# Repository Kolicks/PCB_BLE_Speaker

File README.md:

# 🔊 PCB_BLE_Speaker  
**BLE Audio + USB-C Rechargeable Speaker Board**

---

## 📘 Overview
**PCB_BLE_Speaker** is a compact **BLE audio speaker board** designed in **KiCad 9**, focused on learning about **USB-C**, **battery-powered systems**, **rechargeable devices**, and **audio amplifier integration**.  
The project explores practical design decisions such as **battery connectors**, **charging circuits**, **power protection**, and **audio MCU layout constraints**.

It includes two **MAX98357A** audio MCUs to experiment with both **mono** and **stereo firmware**, and was created as an exercise in **DFM/DFA**, power routing, and EMC-aware PCB design.

<p align="center">
  
  <br>
  <em>3D render of the PCB_BLE_Speaker board</em>
</p>

---

## ⚠️ FLAWS
- Serial Comms does not work, need extra circuitry for EN/BOOT between ESP32 and CP2102N.
- Be aware of the Audio connectors polarity. In this design you may need to solder on the opposite direction.

---

## ⚙️ General Information
- Designed in **KiCad 9** as a learning platform for:
  - USB-C 2.0 (5 V / 1 A)
  - Battery-powered systems
  - Rechargeable device architecture  
- Includes **two battery connectors**:  
  - One for a battery already owned  
  - One for a **standard battery connector** planned for purchase  
- Created to better understand **power protection**, **charging ICs**, and **audio layout constraints**.
- Built on a **4-layer PCB**, as recommended for the **MAX98357A** for better reliability, noise control, and ground integrity.
- All components intentionally placed on the **top layer** as a DFA/DFM exercise.

<p align="center">
  
  <br>
  <em>Schematic (KiCad 9)</em>
</p>

---

## 🔊 Characteristics
- **USB-C 2.0** input supplying **5 V up to 1 A**.  
- **MCP73831-2-OT** Li-Ion charger with a **5 kΩ PROG resistor**, giving a safe **200 mA charge current** — chosen to reduce thermal risks since no temperature monitoring system is implemented.  
- **MOSFET protection circuitry** between USB-C and charger to manage correct power flow and avoid dangerous battery–USB backfeed conditions.  
- **Two MAX98357A audio MCUs** included:
  - Allows experimenting with **mono** and **stereo** BLE audio firmware.
- Intended for **battery operation**:
  - A DC/DC regulator would have improved efficiency, but was intentionally discarded for version 1 for simplicity.
- Observed layout improvement for next revision:
  - Placing **audio amplifier + charger + power supply** side by side to reduce **current loop area**, improving **EMC/EMI** behavior and reducing high-current noise.

<p align="center">
  
  <br>
  <em>PCB layout design</em>
</p>

---

## ⚠️ Known Issues / Notes
- Power architecture can be improved by using a **buck DC/DC converter** for better efficiency during battery operation.  
- Current loops of the audio + charger power path could be optimized by placing related components closer.  
- Future improvements should include:
  - Better **EMI loop minimization**  
  - Dedicated copper pours for high-current paths  
  - Additional filtering  
- Placement of both audio MCUs on the top layer made routing more challenging, but was kept intentionally as a DFM/DFA practice exercise.
- Rechargable Battery circuitry WORKS as expected!
---

## 🧩 Files and Structure

<p align="center">
  
</p>

PCB_BLE_Speaker/
├── schematic/
├── pcb_layout/
├── gerbers/
├── images/
├── LICENSE
└── README.md

---

## 📜 License
This hardware design is released under the **CERN Open Hardware License v2 – Permissive (CERN-OHL-P-2.0)**.  
You may use, modify, and redistribute the design, as long as:
- You include the license in redistributions.
- You give proper credit to the original author.

---

## 👤 Author
**Project:** PCB_BLE_Speaker  
**Author:** Kolicks  
**Toolchain:** KiCad 9  
**Version:** 1.0  

---

## 🧱 Future Improvements
- **Power Efficiency**
  - Add a **buck DC/DC converter** to improve battery runtime and reduce heat.  
- **EMI-Aware Layout**
  - Place **charger + power supply + audio MCUs** adjacently to shrink high-current loops.  
- **User Indicators**
  - Add **charging, power, and battery status LEDs**.  
- **Battery Protection**
  - Add optional **NTC thermistor** for thermal monitoring.  
- **Usability**
  - Improve connector positioning and silkscreen clarity.
  - Add circuitry for Serial to make it reliable.
  - Change MCU to another one more suitable for Hand Soldering.

---

⭐ *If this project interests you, feel free to star the repository or contribute with suggestions!*

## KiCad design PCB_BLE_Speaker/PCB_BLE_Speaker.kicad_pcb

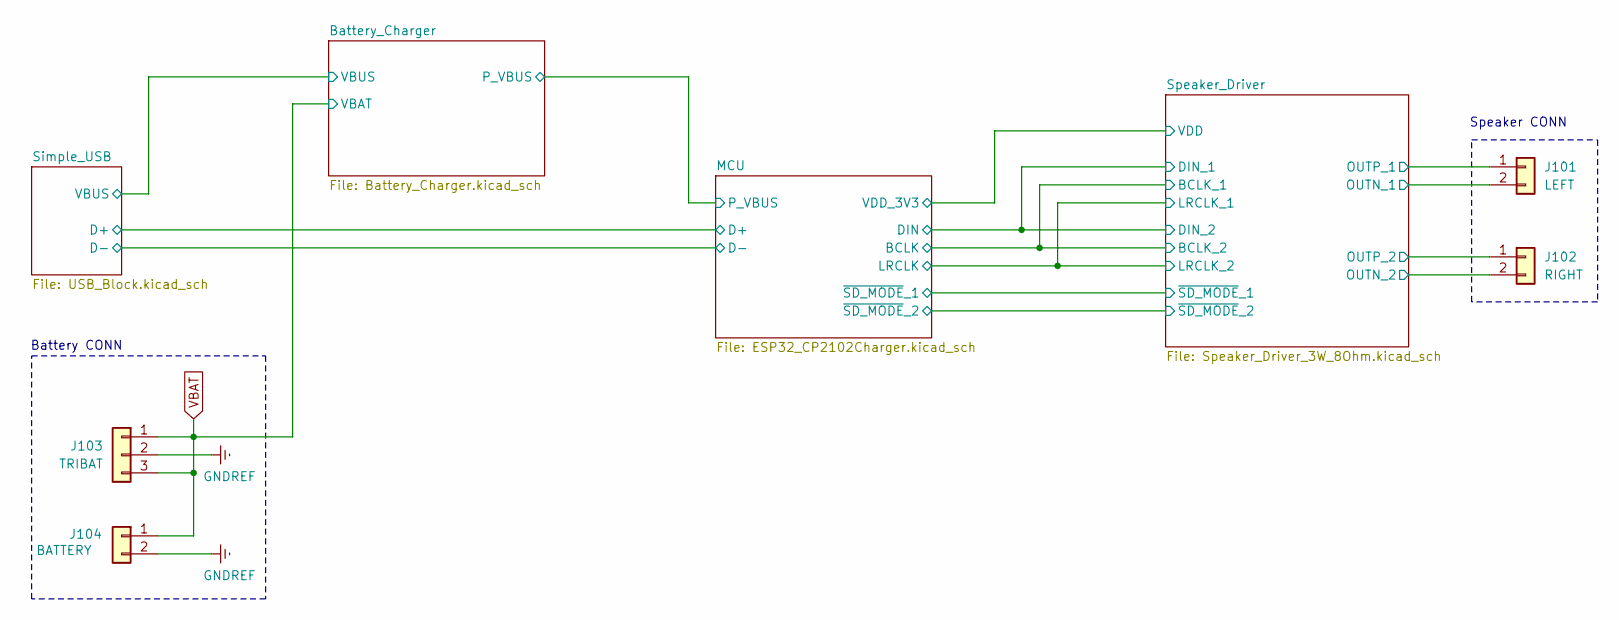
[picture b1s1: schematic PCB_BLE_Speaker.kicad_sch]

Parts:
J101: LEFT; JST_PH_B2B-PH-K_1x02_P2.00mm_Vertical
J102: RIGHT; JST_PH_B2B-PH-K_1x02_P2.00mm_Vertical
J103: TRIBAT; JST_XH_B3B-XH-A_1x03_P2.50mm_Vertical
J104: BATTERY; JST_PH_B2B-PH-K_1x02_P2.00mm_Vertical

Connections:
/Speaker_Driver/OUTN_1: J101.2; also elsewhere on the board
/Speaker_Driver/OUTN_2: J102.2; also elsewhere on the board
/Speaker_Driver/OUTP_1: J101.1; also elsewhere on the board
/Speaker_Driver/OUTP_2: J102.1; also elsewhere on the board
GNDREF: J103.2, J104.2; also elsewhere on the board
VBAT: J103.1, J103.3, J104.1; also elsewhere on the board

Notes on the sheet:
Battery CONN
Speaker CONN

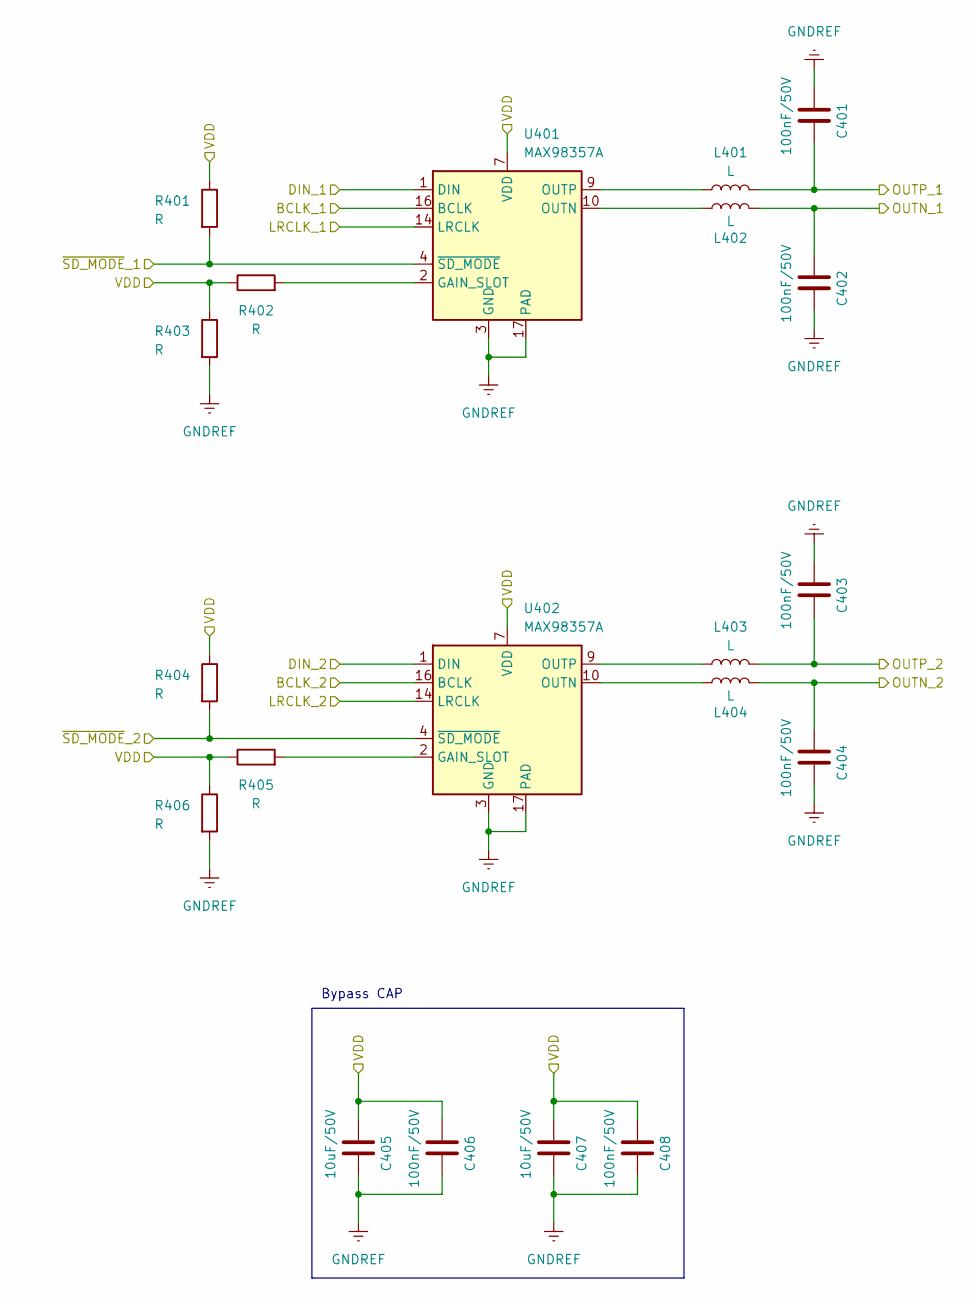
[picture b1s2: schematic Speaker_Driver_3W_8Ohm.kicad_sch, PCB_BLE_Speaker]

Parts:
C401, C402, C403, C404, C406, C408: 100nF/50V; C_0603_1608Metric_Pad1.08x0.95mm_HandSolder
C405, C407: 10uF/50V; C_0603_1608Metric_Pad1.08x0.95mm_HandSolder
L401, L402, L403, L404: L; L_0603_1608Metric_Pad1.05x0.95mm_HandSolder
R401, R402, R403, R404, R405, R406: R; R_0603_1608Metric_Pad0.98x0.95mm_HandSolder
U401, U402: MAX98357A; TQFN-16-1EP_3x3mm_P0.5mm_EP1.23x1.23mm

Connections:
/MCU/BCLK: U401.16 (BCLK), U402.16 (BCLK); also elsewhere on the board
/MCU/DIN: U401.1 (DIN), U402.1 (DIN); also elsewhere on the board
/MCU/LRCLK: U401.14 (LRCLK), U402.14 (LRCLK); also elsewhere on the board
/MCU/VDD_3V3: C405.2, C406.2, C407.2, C408.2, R401.1, R402.1, R403.1, R404.1, R405.1, R406.1, U401.7 (VDD), U401.8 (VDD), U402.7 (VDD), U402.8 (VDD); also elsewhere on the board
/MCU/~SD_MODE_1: R401.2, U401.4 (~SD_MODE); also elsewhere on the board
/MCU/~SD_MODE_2: R404.2, U402.4 (~SD_MODE); also elsewhere on the board
/Speaker_Driver/OUTN_1: C402.2, L402.2; also elsewhere on the board
/Speaker_Driver/OUTN_2: C404.2, L404.2; also elsewhere on the board
/Speaker_Driver/OUTP_1: C401.1, L401.2; also elsewhere on the board
/Speaker_Driver/OUTP_2: C403.1, L403.2; also elsewhere on the board
GNDREF: C401.2, C402.1, C403.2, C404.1, C405.1, C406.1, C407.1, C408.1, R403.2, R406.2, U401.3 (GND), U401.11 (GND), U401.15 (GND), U401.17 (PAD), U402.3 (GND), U402.11 (GND), U402.15 (GND), U402.17 (PAD); also elsewhere on the board
unnamed: R402.2, U401.2 (GAIN_SLOT)
unnamed: L402.1, U401.10 (OUTN)
unnamed: L401.1, U401.9 (OUTP)
unnamed: R405.2, U402.2 (GAIN_SLOT)
unnamed: L404.1, U402.10 (OUTN)
unnamed: L403.1, U402.9 (OUTP)

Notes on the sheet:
Bypass CAP

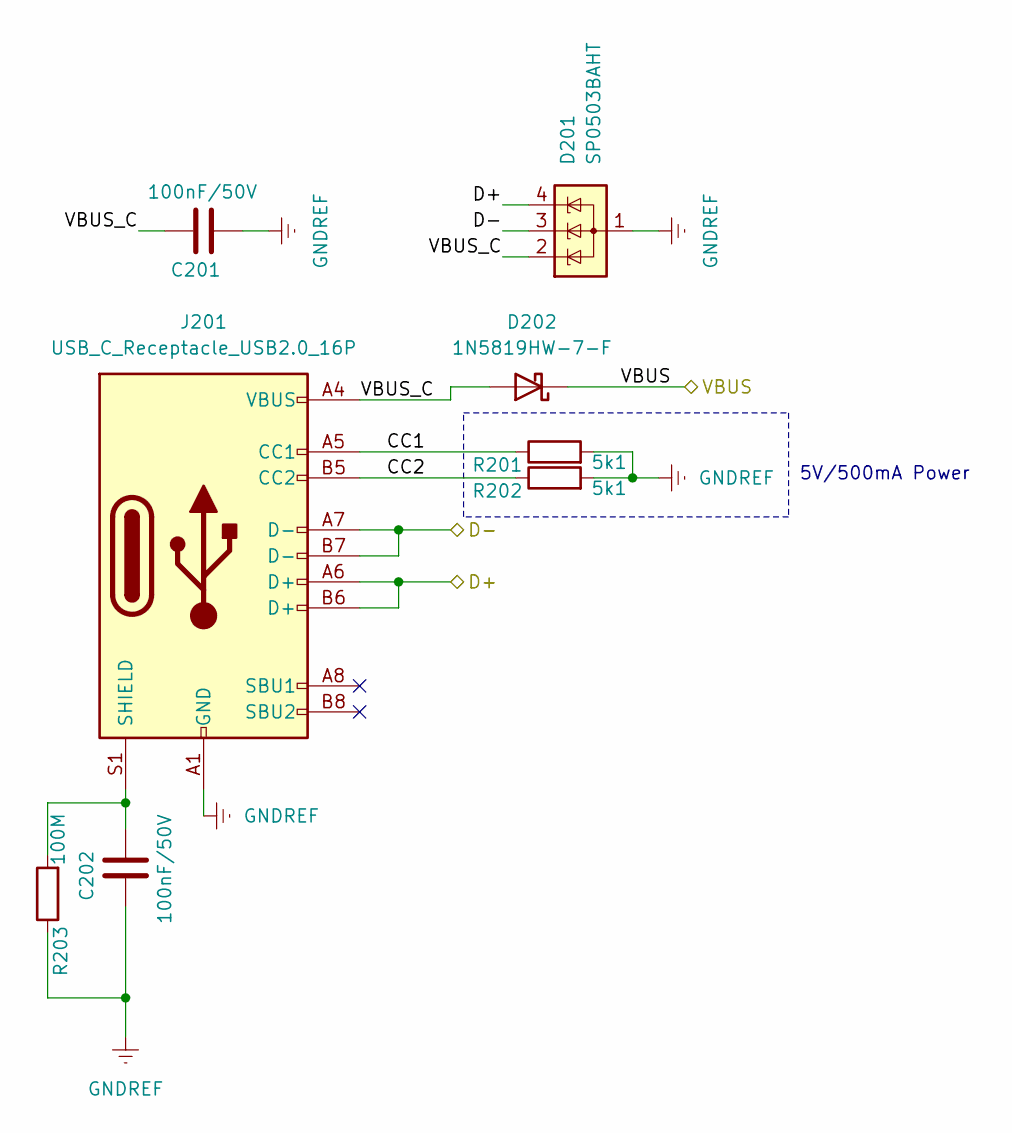
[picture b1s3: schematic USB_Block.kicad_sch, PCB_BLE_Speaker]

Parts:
C201, C202: 100nF/50V; C_0603_1608Metric_Pad1.08x0.95mm_HandSolder
D201: SP0503BAHT; SOT-143_Handsoldering
D202: 1N5819HW-7-F; D_SOD-123F
J201: USB_C_Receptacle_USB2.0_16P; USB_C_Receptacle_GCT_USB4105-xx-A_16P_TopMnt_Horizontal
R201, R202: 5k1; R_0603_1608Metric_Pad0.98x0.95mm_HandSolder
R203: 100M; R_0603_1608Metric_Pad0.98x0.95mm_HandSolder

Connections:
/Simple_USB/CC1: J201.A5 (CC1), R201.1
/Simple_USB/CC2: J201.B5 (CC2), R202.1
/Simple_USB/D+: D201.4 (K), J201.A6 (D+), J201.B6 (D+); also elsewhere on the board
/Simple_USB/D-: D201.3 (K), J201.A7 (D-), J201.B7 (D-); also elsewhere on the board
/Simple_USB/VBUS: D202.1 (K); also elsewhere on the board
/Simple_USB/VBUS_C: C201.1, D201.2 (K), D202.2 (A), J201.A4 (VBUS), J201.A9 (VBUS), J201.B4 (VBUS), J201.B9 (VBUS)
GNDREF: C201.2, C202.1, D201.1 (A), J201.A1 (GND), J201.A12 (GND), J201.B1 (GND), J201.B12 (GND), R201.2, R202.2, R203.1; also elsewhere on the board
unnamed: C202.2, J201.S1 (SHIELD), R203.2

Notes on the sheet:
5V/500mA Power

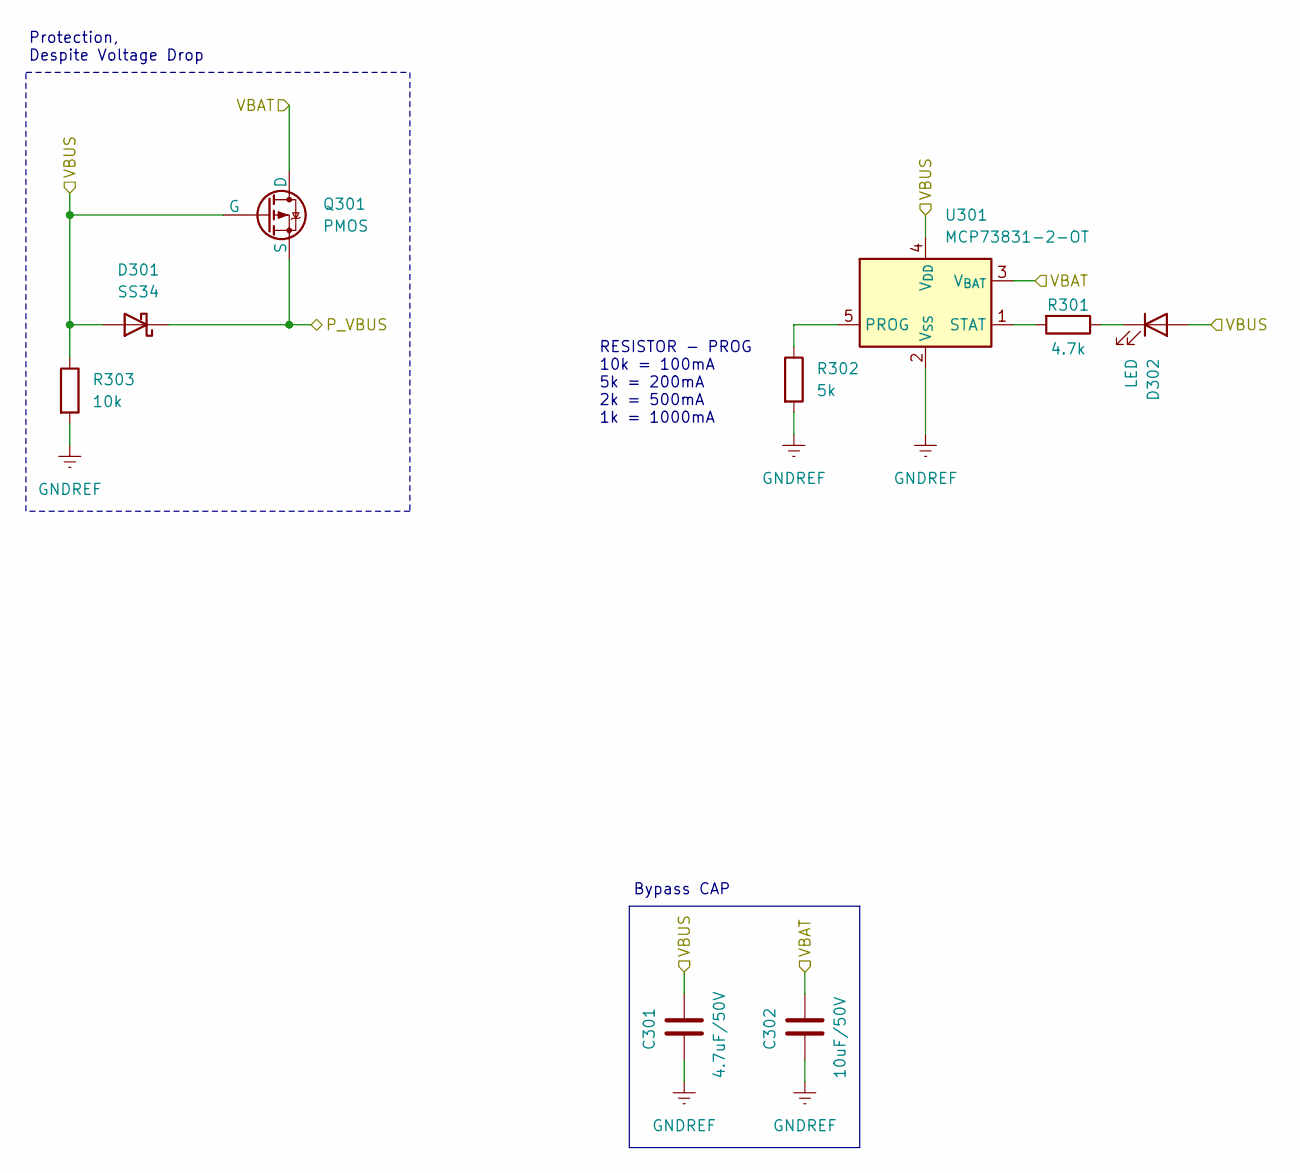
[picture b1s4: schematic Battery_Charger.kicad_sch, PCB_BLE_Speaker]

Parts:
C301: 4.7uF/50V; C_0603_1608Metric_Pad1.08x0.95mm_HandSolder
C302: 10uF/50V; C_0603_1608Metric_Pad1.08x0.95mm_HandSolder
D301: SS34; D_SMA_Handsoldering
D302: LED; LED_0603_1608Metric_Pad1.05x0.95mm_HandSolder
Q301: PMOS; SOT-223_ISP20EP10LMXTSA1
R301: 4.7k; R_0603_1608Metric_Pad0.98x0.95mm_HandSolder
R302: 5k; R_0603_1608Metric_Pad0.98x0.95mm_HandSolder
R303: 10k; R_0603_1608Metric_Pad0.98x0.95mm_HandSolder
U301: MCP73831-2-OT; SOT-23-5_HandSoldering

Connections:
/Battery_Charger/P_VBUS: D301.1 (K), Q301.3 (S); also elsewhere on the board
/Simple_USB/VBUS: C301.1, D301.2 (A), D302.2 (A), Q301.2 (G), R303.1, U301.4 (V_{DD}); also elsewhere on the board
GNDREF: C301.2, C302.2, R302.2, R303.2, U301.2 (V_{SS}); also elsewhere on the board
unnamed: D302.1 (K), R301.1
unnamed: R302.1, U301.5 (PROG)
unnamed: R301.2, U301.1 (STAT)
VBAT: C302.1, Q301.1 (D), U301.3 (V_{BAT}); also elsewhere on the board

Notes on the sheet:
Bypass CAP
Protection, Despite Voltage Drop
RESISTOR - PROG 10k = 100mA 5k = 200mA 2k = 500mA 1k = 1000mA

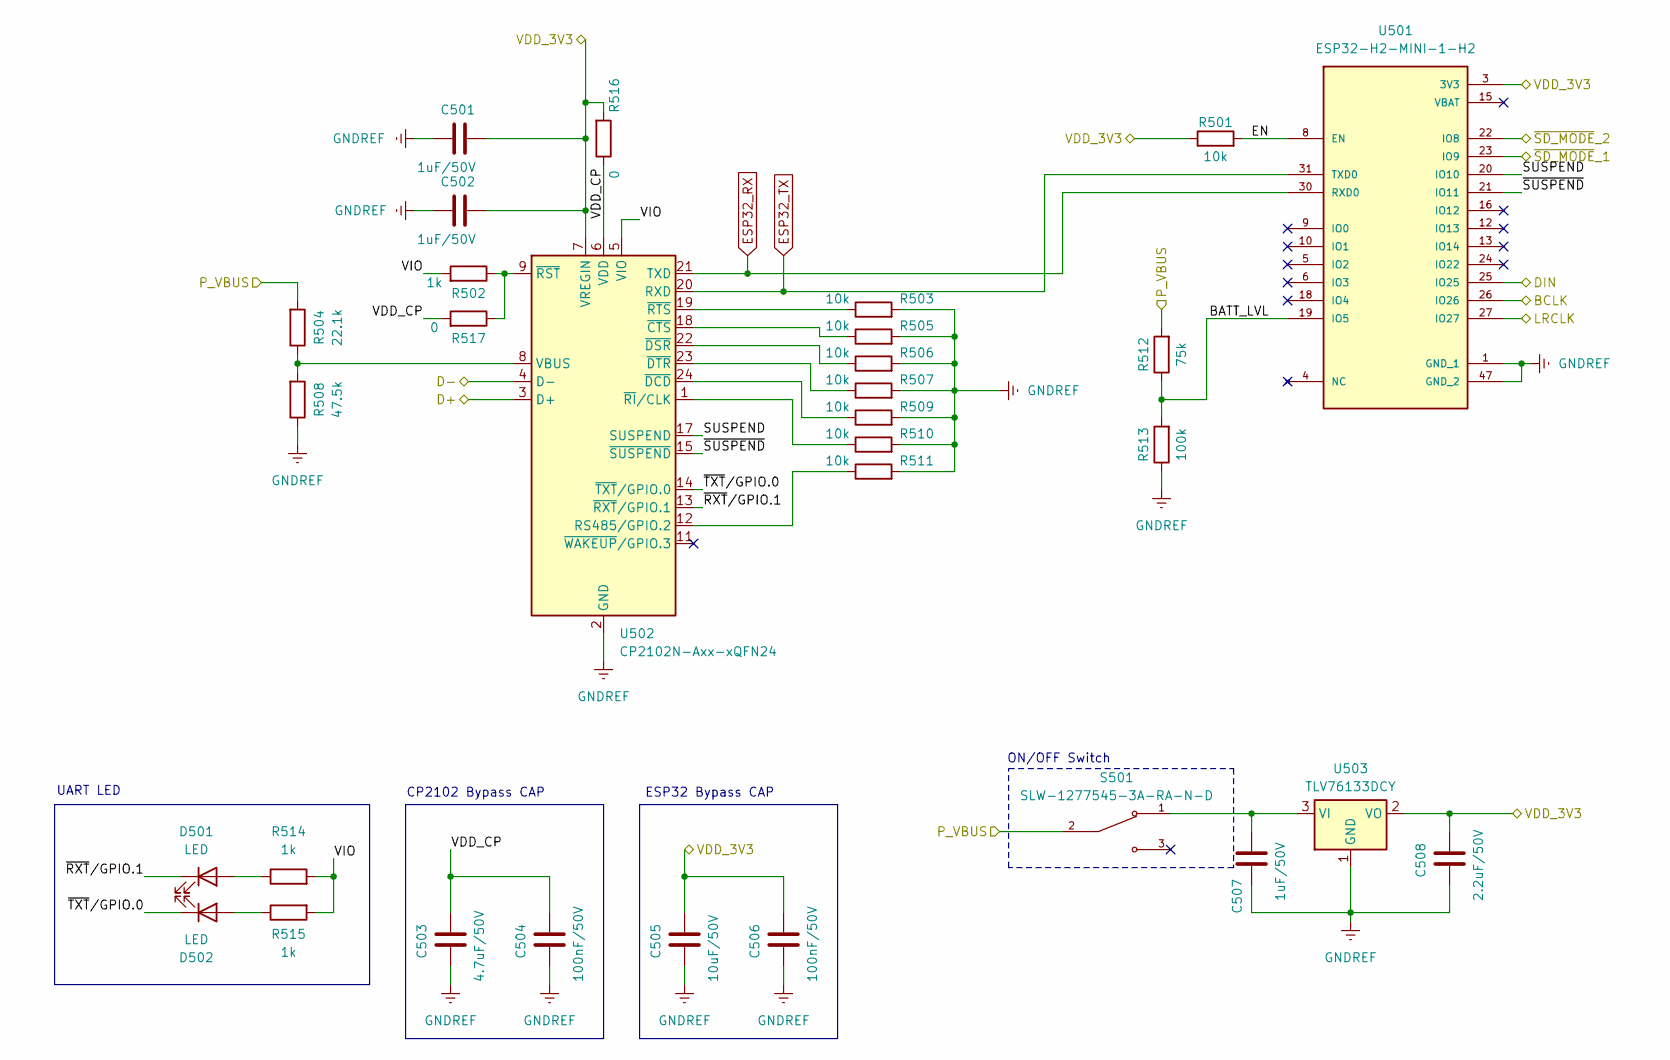
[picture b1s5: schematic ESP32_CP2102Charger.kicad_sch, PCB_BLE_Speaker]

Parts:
C501, C502, C507: 1uF/50V; C_0603_1608Metric_Pad1.08x0.95mm_HandSolder
C503: 4.7uF/50V; C_0603_1608Metric_Pad1.08x0.95mm_HandSolder
C504, C506: 100nF/50V; C_0603_1608Metric_Pad1.08x0.95mm_HandSolder
C505: 10uF/50V; C_0603_1608Metric_Pad1.08x0.95mm_HandSolder
C508: 2.2uF/50V; C_0603_1608Metric_Pad1.08x0.95mm_HandSolder
D501, D502: LED; LED_0603_1608Metric_Pad1.05x0.95mm_HandSolder
R501, R503, R505, R506, R507, R509, R510, R511: 10k; R_0603_1608Metric_Pad0.98x0.95mm_HandSolder
R502, R514, R515: 1k; R_0603_1608Metric_Pad0.98x0.95mm_HandSolder
R504: 22.1k; R_0603_1608Metric_Pad0.98x0.95mm_HandSolder
R508: 47.5k; R_0603_1608Metric_Pad0.98x0.95mm_HandSolder
R512: 75k; R_0603_1608Metric_Pad0.98x0.95mm_HandSolder
R513: 100k; R_0603_1608Metric_Pad0.98x0.95mm_HandSolder
R516, R517: 0; R_0603_1608Metric_Pad0.98x0.95mm_HandSolder
S501: SLW-1277545-3A-RA-N-D; SW_SLW-1277545-3A-RA-N-D; PARTREV 1.01
U501: ESP32-H2-MINI-1-H2; MODULE_ESP32-H2-MINI-1-H2_NO_Thermal; PARTREV v0.5
U502: CP2102N-Axx-xQFN24; QFN-24-1EP_4x4mm_P0.5mm_EP2.65x2.65mm
U503: TLV76133DCY; SOT-223-3_TabPin2

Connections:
/Battery_Charger/P_VBUS: R504.2, R512.2, S501.2; also elsewhere on the board
/MCU/BATT_LVL: R512.1, R513.2, U501.19 (IO5)
/MCU/BCLK: U501.26 (IO26); also elsewhere on the board
/MCU/DIN: U501.25 (IO25); also elsewhere on the board
/MCU/EN: R501.2, U501.8 (EN)
/MCU/LRCLK: U501.27 (IO27); also elsewhere on the board
/MCU/SUSPEND: U501.20 (IO10), U502.17 (SUSPEND)
/MCU/VDD_3V3: C501.1, C502.1, C505.1, C506.1, C508.1, R501.1, R516.2, U501.3 (3V3), U502.7 (VREGIN), U503.2 (VO); also elsewhere on the board
/MCU/VDD_CP: C503.1, C504.1, R516.1, R517.2, U502.6 (VDD)
/MCU/VIO: R502.2, R514.2, R515.2, U502.5 (VIO)
/MCU/~RXT/GPIO.1: D501.1 (K), U502.13 (~RXT/GPIO.1)
/MCU/~SD_MODE_1: U501.23 (IO9); also elsewhere on the board
/MCU/~SD_MODE_2: U501.22 (IO8); also elsewhere on the board
/MCU/~SUSPEND: U501.21 (IO11), U502.15 (~SUSPEND)
/MCU/~TXT/GPIO.0: D502.1 (K), U502.14 (~TXT/GPIO.0)
/Simple_USB/D+: U502.3 (D+); also elsewhere on the board
/Simple_USB/D-: U502.4 (D-); also elsewhere on the board
ESP32_RX: U501.30 (RXD0), U502.21 (TXD)
ESP32_TX: U501.31 (TXD0), U502.20 (RXD)
GNDREF: C501.2, C502.2, C503.2, C504.2, C505.2, C506.2, C507.2, C508.2, R503.2, R505.2, R506.2, R507.2, R508.1, R509.2, R510.2, R511.2, R513.1, U501.1 (GND_1), U501.47 (GND_2), U502.2 (GND), U502.25 (GND), U503.1 (GND); also elsewhere on the board
NC: U501.4 (NC), U501.7 (NC)
unnamed: D501.2 (A), R514.1
unnamed: D502.2 (A), R515.1
unnamed: R511.1, U502.12 (RS485/GPIO.2)
unnamed: R504.1, R508.2, U502.8 (VBUS)
unnamed: R505.1, U502.18 (~CTS)
unnamed: R509.1, U502.24 (~DCD)
unnamed: R506.1, U502.22 (~DSR)
unnamed: R507.1, U502.23 (~DTR)
unnamed: R510.1, U502.1 (~RI/CLK)
unnamed: R502.1, R517.1, U502.9 (~RST)
unnamed: R503.1, U502.19 (~RTS)
unnamed: C507.1, S501.1, U503.3 (VI)

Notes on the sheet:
CP2102 Bypass CAP
UART LED
ON/OFF Switch
ESP32 Bypass CAP

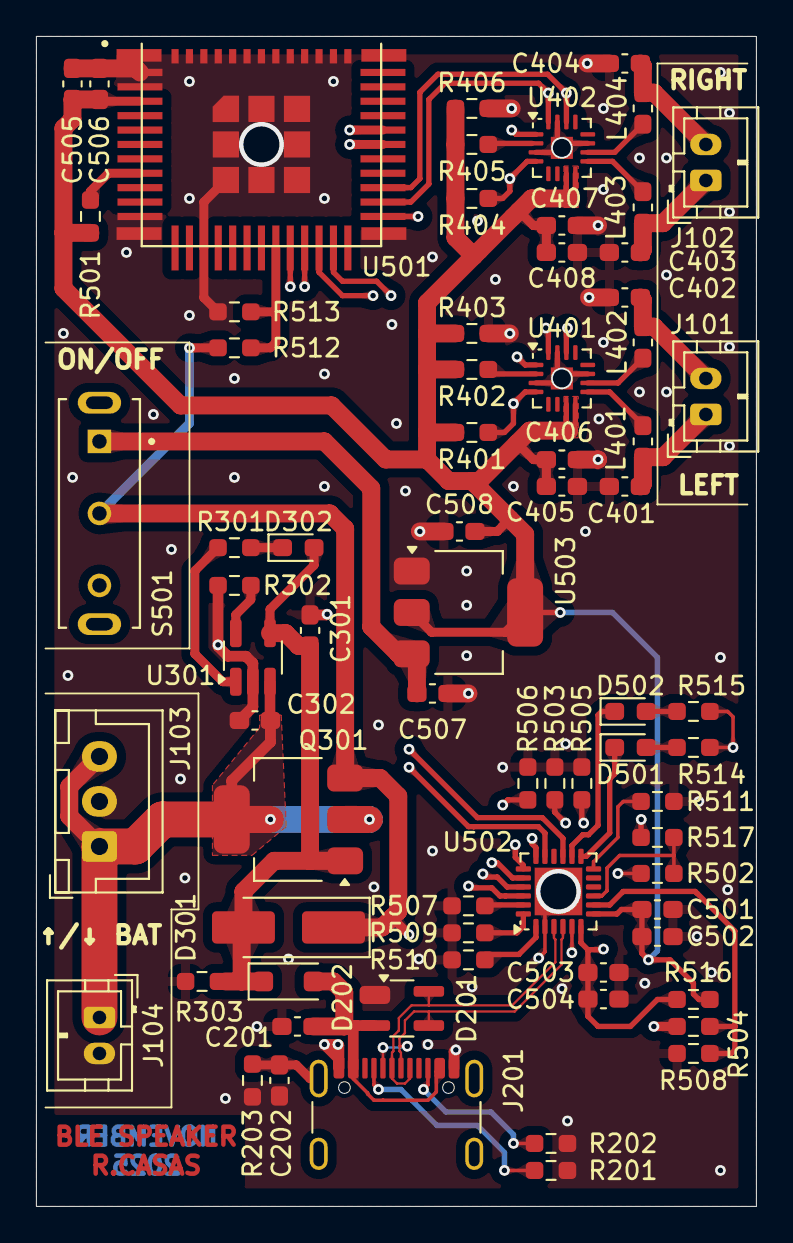
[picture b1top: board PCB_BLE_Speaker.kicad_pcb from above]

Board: 4 copper layers, 40.0 x 65.0 mm, 72 parts (0 on the bottom side), 51 nets.

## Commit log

2025-12-11 Update README to remove PCB production note
    Removed production test note from README.
2025-12-11 Update README with rechargeable battery status
    Updated README to reflect working rechargeable battery circuitry.
2025-12-11 Enhance usability with Serial circuitry and MCU change
    Added circuitry for Serial reliability and changed MCU for better hand soldering.
